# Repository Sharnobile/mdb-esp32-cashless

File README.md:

<div align="center">

# VMflow

### Open-Source Vending Machine IoT Platform

**Turn any vending machine into a connected, cashless, remotely managed device.**

**[🌐 Live Dashboard](https://app.kerl-handel.de)** · [⚡ Web Installer](https://app.kerl-handel.de/install) · [📖 Local Dev](DEV.md) · [🚀 Production](PROD.md) · [🏗 Architecture](ARCHITECTURE.md)

</div>

---

VMflow is a complete, **self-hostable** platform for retrofitting ordinary vending machines with modern IoT capabilities. A custom **ESP32-S3** board plugs into any machine's **MDB (Multi-Drop Bus)** and instantly unlocks cashless payments, real-time sales tracking, remote credit delivery, over-the-air firmware updates, warehouse-driven refills, foot-traffic analytics, and AI-powered insights — all controlled from a modern web dashboard and a native iOS app.

No vendor lock-in, no cloud subscription, no per-device fees. You own the hardware, the firmware, the backend, and the data.

---

## ✨ What You Can Do

<table>
<tr>
<td width="50%" valign="top">

### 🏪 Fleet & Machine Management
Monitor every machine in real time — online/offline status, today/this-week/this-month revenue, sales counts, and which machines need refilling. Drill into any machine for a 30-day revenue chart and an itemized, time-stamped sales history.

</td>
<td width="50%" valign="top">

### 💳 Cashless Payments (MDB)
A standards-compliant MDB **cashless peripheral**. Deliver credit to a machine remotely over MQTT or BLE, sit alongside existing coin/bill acceptors, and approve vends in real time. All payloads are XOR-encrypted with replay protection.

</td>
</tr>
<tr>
<td width="50%" valign="top">

### 📦 Warehouse & Inventory
Barcode-driven stock intake, **FIFO batch tracking** with expiry dates, per-warehouse minimum-stock alerts, stock-value reporting, and physical position layouts. Stock auto-decrements on every sale.

</td>
<td width="50%" valign="top">

### 🔁 Guided Refill Tours
A step-by-step refill wizard generates per-machine packing lists from live warehouse stock, walks the operator through the route, deducts inventory FIFO, and logs the whole tour for history and audit.

</td>
</tr>
<tr>
<td width="50%" valign="top">

### 🤖 AI Insights
Per-machine and fleet-wide recommendations powered by the **Claude API** — spot dead slots, surface best-sellers, and get concrete product-swap suggestions, in your own language. Bring your own API key.

</td>
<td width="50%" valign="top">

### 🧾 Sales Reconciliation
Upload a **Nayax** sales export and reconcile it against recorded sales with a time-tolerant matcher. Bulk-import anything missing, remove ghost entries, and export a CSV diff — fully audited.

</td>
</tr>
<tr>
<td width="50%" valign="top">

### 📊 Telemetry & Foot Traffic
Read **EVA-DTS DEX/DDCMP** data straight off the machine, count nearby foot traffic with the **PAX Counter** (anonymized BLE/WiFi presence), and keep a full MDB bus diagnostics + state history per device.

</td>
<td width="50%" valign="top">

### 🔄 OTA & Firmware
Build firmware in **GitHub Actions**, import a release with one click, and deploy **over-the-air** to any device over MQTT. Full/app-only images, version notes, and per-version rollout control.

</td>
</tr>
<tr>
<td width="50%" valign="top">

### 📡 Resilient Connectivity
WiFi out of the box, with optional **Cellular / LTE** (SIM7080G Cat-M / NB-IoT) for machines without a network. A multi-layer recovery ladder keeps devices online unattended in the field.

</td>
<td width="50%" valign="top">

### 🏢 Multi-Tenancy & Security
Organization-based access with **admin/viewer** roles, email invitations, and **row-level security** on every table. Self-hosted auth, storage, and database — your data never leaves your server.

</td>
</tr>
</table>

---

## 🖥 Management Dashboard

A modern, responsive web app (Nuxt 4 PWA, installable, dark mode, English & German) that gives operators full control over their fleet.

> **[👉 See it live at app.kerl-handel.de](https://app.kerl-handel.de)**

<table>
<tr>
<td width="50%" align="center" valign="top">

**Fleet overview** — live status, per-machine revenue, and stock urgency at a glance

</td>
<td width="50%" align="center" valign="top">

**Machine detail** — 30-day revenue chart and itemized sales history with product images

</td>
</tr>
<tr>
<td width="50%" align="center" valign="top">

**Product analysis** — springboard layout colour-coded by performance, with one-click swaps

</td>
<td width="50%" align="center" valign="top">

**Warehouse** — stock levels, FIFO batches, expiry warnings, and live stock value

</td>
</tr>
<tr>
<td width="50%" align="center" valign="top">

**Guided refill tour** — per-machine packing lists driven by live warehouse availability

</td>
<td width="50%" align="center" valign="top">

**Product catalog** — images, categories, pricing, and bulk Nayax import

</td>
</tr>
<tr>
<td width="50%" align="center" valign="top">

**Dashboard** — revenue KPIs, 7-day trend, and best-selling products

</td>
<td width="50%" align="center" valign="top">

**Firmware & OTA** — import from GitHub releases and deploy over-the-air

</td>
</tr>
</table>

---

## 📱 iOS App

A native **SwiftUI** app for operators — full fleet management from your pocket.

- **Dashboard** — revenue KPIs, 30-day sales chart, recent-sales feed
- **Machines** — sorted by stock urgency, with warehouse-availability labels
- **Trays & Stock** — per-machine slot configuration and quick stock adjustments
- **Refill Wizard** — warehouse-aware packing, guided refill tour, and a review step
- **Sales Stats** — today / yesterday / this week / last week per machine

Built with SwiftUI, Swift Concurrency, the Supabase Swift SDK, and Swift Charts. See [`ios/README.md`](ios/README.md) for setup.

<!--
  📸 iOS SCREENSHOTS
  Drop device screenshots into docs/screenshots/ios/ and uncomment the gallery below.

<table>
<tr>
<td width="33%" align="center"><br/><b>Dashboard</b></td>
<td width="33%" align="center"><br/><b>Machines</b></td>
<td width="33%" align="center"><br/><b>Refill Wizard</b></td>
</tr>
</table>
-->

> 📲 _App screenshots are being added — coming soon._

---

## 🤖 Android App

A native Android app is on the roadmap. **Coming soon.**

---

## 🔌 Hardware

The custom PCB connects directly to the vending machine's MDB bus via the standard connector. It's powered from the machine's own supply, needs no external power, and talks to the backend over WiFi (or optional Cellular/LTE) + MQTT.

<table>
<tr>
<td width="33%" align="center" valign="top">

**PCB v3** — latest revision

</td>
<td width="33%" align="center" valign="top">

**Installed** — with 3D-printed mount

</td>
<td width="33%" align="center" valign="top">

**Mounting bracket** — printable STL included

</td>
</tr>
</table>

**Key specs**

- **MCU:** ESP32-S3 (dual-core, WiFi + BLE 5)
- **MDB interface:** UART 9600 baud, 9-bit mode, optocoupler isolated
- **Power:** drawn from the vending-machine bus (onboard buck converter)
- **Connectivity:** WiFi, optional Cellular/LTE (SIM7080G Cat-M / NB-IoT)
- **Connectors:** MDB, USB-C (programming & debug), DEX telemetry port
- **PCB design:** KiCad — sources in [`kicad/`](kicad/)
- **Enclosure:** 3D-printable bracket — STL/STEP in [`3d-printing/`](3d-printing/)

> 🛒 **Order the PCB:** [PCBWay shared project](https://www.pcbway.com/project/shareproject/mdb_esp32_cashless_bc6bf8d8.html)

---

## 🏗 How It Works

```
┌───────────────────────────────────────────────────────────────────┐
│                       Management UI (Nuxt 4)  ·  iOS App (SwiftUI)  │
│            Dashboard · Machines · Warehouse · Refill · Firmware     │
└──────────────────────────────┬────────────────────────────────────┘
                               │ HTTPS
                               ▼
┌─────────────────────────────────────────────────────────────────────┐
│                       Supabase (self-hosted)                          │
│   ┌──────────┐  ┌──────────┐  ┌────────────────┐  ┌───────────────┐  │
│   │  Kong    │  │  Auth    │  │ Edge Functions  │  │   Storage     │  │
│   │ API GW   │  │ (GoTrue) │  │     (Deno)      │  │ firmware/imgs │  │
│   └──────────┘  └──────────┘  └────────┬────────┘  └───────────────┘  │
│   ┌─────────────────────────────────────────────────────────────┐    │
│   │            PostgreSQL  (RLS + multi-tenancy)                 │    │
│   └─────────────────────────────────────────────────────────────┘    │
└──────────────────────────────┬────────────────────────────────────────┘
                               │
            ┌──────────────────┼──────────────────┐
            ▼                  ▼                  ▼
┌──────────────────┐  ┌──────────────┐  ┌──────────────────────┐
│  MQTT Forwarder  │  │ MQTT Broker  │  │   GitHub Actions     │
│     (Deno)       │  │ (Mosquitto)  │  │   CI/CD → Releases   │
│  MQTT → Webhook  │  │    :1883     │  │   (firmware builds)  │
└──────────────────┘  └──────┬───────┘  └──────────────────────┘
                             │  MQTT over WiFi / Cellular
              ┌──────────────┴──────────────┐
              ▼                             ▼
   ┌──────────────────────┐     ┌──────────────────────┐
   │   ESP32-S3 (Slave)   │     │   ESP32-S3 (Slave)   │
   │   MDB Cashless       │ ··· │   MDB Cashless       │
   │  ┌────────────────┐  │     │  ┌────────────────┐  │
   │  │ Vending Machine│  │     │  │ Vending Machine│  │
   │  └────────────────┘  │     │  └────────────────┘  │
   └──────────────────────┘     └──────────────────────┘
```

Devices publish sales, status, telemetry, and diagnostics to per-tenant MQTT topics (`/{company}/{device}/{event}`). A Deno forwarder bridges MQTT to a Supabase Edge Function that decrypts, validates, and writes to PostgreSQL. Sensitive payloads (credit, sales, config) are **XOR-encrypted** with an 18-byte passkey and an ±8-second timestamp window to prevent replay. See [ARCHITECTURE.md](ARCHITECTURE.md) for the full picture.

---

## 🚀 Getting Started

### 1. Flash the firmware

The easiest way — no build tools required:

👉 **[app.kerl-handel.de/install](https://app.kerl-handel.de/install)** — flash directly from your browser via Web Serial

Or build from source with ESP-IDF v5.x:

```bash
cd mdb-slave-esp32s3
. $IDF_PATH/export.sh
idf.py build flash monitor
```

### 2. Deploy the platform

Pick the setup that fits your use case:

| | **Local Development** | **Production** |
|---|---|---|
| **Guide** | 📖 [**DEV.md**](DEV.md) | 🚀 [**PROD.md**](PROD.md) |
| **Purpose** | Develop & test locally | Deploy for real devices |
| **Backend** | Supabase CLI (`supabase start`) | Docker Compose (`docker compose up`) |
| **Frontend** | `npm run dev` (hot reload) | Built & served via Docker |
| **Setup** | `supabase start` + `npm run dev` | `bash setup.sh` (one command) |

### 3. Provision a device

Once the platform is running:

1. Power on the ESP32 board → it creates a WiFi hotspot
2. Connect to the hotspot and open the captive portal → enter WiFi credentials + server URL
3. In the dashboard, go to **Devices** → generate a provisioning code
4. Enter the code on the device's captive portal
5. The device reboots, connects to MQTT, and appears in your dashboard

---

## 🔗 REST API

VMflow exposes a full REST API via Supabase. Authenticate with a JWT bearer token.

<details>
<summary><strong>Get a bearer token</strong></summary>

```bash
curl -X POST 'https://your-server:8000/auth/v1/token?grant_type=password' \
  -H "apikey: YOUR_ANON_KEY" \
  -H "Content-Type: application/json" \
  -d '{ "email": "you@example.com", "password": "your_password" }'
```
</details>

<details>
<summary><strong>Send credit to a machine</strong></summary>

```bash
curl -X POST 'https://your-server:8000/functions/v1/send-credit' \
  -H "apikey: YOUR_ANON_KEY" \
  -H "Authorization: Bearer YOUR_ACCESS_TOKEN" \
  -H "Content-Type: application/json" \
  -d '{ "subdomain": 51, "amount": 1.50 }'
```
</details>

<details>
<summary><strong>View sales</strong></summary>

```bash
curl -X GET 'https://your-server:8000/rest/v1/sales' \
  -H "apikey: YOUR_ANON_KEY" \
  -H "Authorization: Bearer YOUR_ACCESS_TOKEN"
```
</details>

<details>
<summary><strong>View devices</strong></summary>

```bash
curl -X GET 'https://your-server:8000/rest/v1/embeddeds' \
  -H "apikey: YOUR_ANON_KEY" \
  -H "Authorization: Bearer YOUR_ACCESS_TOKEN"
```
</details>

---

## 🗺 PAX Counter — Foot-Traffic Heatmap

Each device scans for nearby BLE/WiFi devices and reports anonymized presence counts, visualized as heatmaps for location-performance analysis.

---

## 📂 Project Structure

```
mdb-esp32-cashless/
├── mdb-slave-esp32s3/       # ESP32 firmware — MDB cashless peripheral
├── mdb-master-esp32s3/      # ESP32 firmware — VMC simulator (for testing)
├── management-frontend/     # Nuxt 4 management dashboard (PWA)
├── ios/                     # Native iOS app (SwiftUI)
├── Docker/                  # Self-hosted backend (docker-compose)
│   ├── supabase/            # Edge functions, migrations, config
│   ├── mqtt/                # Mosquitto broker + Deno forwarder
│   └── setup.sh             # One-command production setup
├── kicad/                   # PCB design files (KiCad)
├── 3d-printing/             # Mounting bracket (STL/STEP/F3D)
├── docs/                    # Screenshots & documentation assets
├── .github/workflows/       # CI/CD — automated firmware builds
├── DEV.md                   # Local development guide
├── PROD.md                  # Production deployment guide
└── ARCHITECTURE.md          # System architecture details
```

---

## 🧰 Tech Stack

| Layer | Technology |
|-------|-----------|
| **Firmware** | ESP-IDF v5.x, FreeRTOS, NimBLE, MQTT, SIM7080G (cellular) |
| **Backend** | Supabase (PostgreSQL, GoTrue, PostgREST, Kong, Edge Functions) |
| **Edge Functions** | Deno (TypeScript) |
| **Frontend** | Nuxt 4, TypeScript, shadcn-vue, TailwindCSS 4, PWA, i18n (en/de) |
| **MQTT** | Eclipse Mosquitto + custom Deno forwarder |
| **AI** | Claude API (machine & fleet insights) |
| **PCB** | KiCad |
| **CI/CD** | GitHub Actions (ESP-IDF builds → GitHub Releases) |
| **iOS App** | SwiftUI, Swift Concurrency, Supabase Swift SDK, Swift Charts |

---

## 🤝 Contributing

Contributions are welcome — firmware, dashboard features, PCB revisions, docs, or bug fixes.

1. **Fork** the repository
2. Set up your [local development environment](DEV.md)
3. Create a feature branch (`git checkout -b feature/my-feature`)
4. Make your changes and ensure the build passes
5. Open a Pull Request

---

## 🙏 Acknowledgments

VMflow began as a fork of **[nodestark/mdb-esp32-cashless](https://github.com/nodestark/mdb-esp32-cashless)**.

Huge thanks to **[@nodestark](https://github.com/nodestark)** for the original open-source MDB cashless implementation for the ESP32 — the protocol foundation that everything here is built on. This project would not exist without that work. 🙌

---

## 📄 License

Licensed under the **MIT License** — see [LICENSE](LICENSE).

Original work Copyright © 2025 Nodestark. VMflow additions © 2025–2026 the VMflow contributors.

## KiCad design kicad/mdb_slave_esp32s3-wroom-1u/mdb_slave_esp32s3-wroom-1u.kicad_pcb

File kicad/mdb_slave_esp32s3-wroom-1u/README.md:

# MDB ESP32-S3 Cashless Module

Custom PCB adding cashless payment and telemetry to vending machines via the **MDB (Multi-Drop Bus)** protocol. Built around an **ESP32-S3-WROOM-1U** module with external antenna. Designed in KiCad 10.

Target platform: any vending machine equipped with an MDB bus. Backend (Supabase + MQTT + Nuxt, Dockerized) is out of scope for this repo.

Base reference: [lucienkerl/mdb-esp32-cashless](https://github.com/lucienkerl/mdb-esp32-cashless).

## Status

- Schematic: complete — ERC has 4 minor housekeeping items left (floating power symbols / an
  unconnected test pad, no real connectivity impact)
- PCB layout: routed, 4-layer board, 149.8 × 38.5 mm — schematic and PCB are in sync (all
  references renumbered and re-synced in rev1.4, including the previously-orphaned 1-Wire
  pull-up R4)
- Revision: **1.4.1** (R26/R28 changed from 10KΩ to 1KΩ)
- Gerbers in `gerber_to_order/` (JLCPCB, PCBWay) reflect the current board

## Overview

The board sits between the vending machine's MDB bus and a cashless payment terminal / telemetry stack. It reads and drives the machine's MDB peripherals, exposes auxiliary sensor and actuator interfaces (1-Wire, I2C, relays, custom digital inputs), and connects to WiFi for backend communication.

Key design decisions:

- **ESP32-S3-WROOM-1U-N16R2** module (16MB flash / 2MB PSRAM) with external u.FL antenna, chosen over a bare ESP32-S3 die because vending machine enclosures are often metal and block internal WiFi.
- **4-layer PCB**, for a dedicated ground/power plane structure and better EMI control around the switching regulator and MDB interface.
- All field connectors placed at the board edge for easy wiring and to fit inside a 3D-printed enclosure.
- Physical separation between the MDB (isolated, high-voltage) side and the logic side, matching the optocoupler isolation barrier in the schematic.

## Functional blocks

**MCU — U1**
ESP32-S3-WROOM-1U-N16R2, with EN/BOOT reset circuit (buttons B1/B2, pull-ups R1/R2/R10, decoupling C1–C3). Onboard WS2812B-compatible RGB status LED (LED1, driven by GPIO21).

**Power**
- F2: PTC resettable fuse on the incoming MDB-side supply
- U8: AP63201WU-7 buck converter, input 3.8V–32V, output 3.3V — **adjustable-output part** (rev1.4, replaces the fixed-output AP63203QWU-7), set by an external feedback divider: R23 (196kΩ, top) / R24 (62kΩ, bottom), with C19 (100pF) as feed-forward capacitor across R23
- C6 (10µF input), C7 (100nF bootstrap), C8/C9 (2×22µF output), L1 (3.3µH inductor)
- Switching loop (U8–L1–output) kept as compact as possible — primary EMI concern

**USB-C — USBC1**
USB 2.0 receptacle for programming/debug, with D6 Schottky diode against VBUS backfeed and R21/R22 CC pull-downs.

**MDB interface — H1**
2×3 connector. Galvanically isolated via U5/U6 (TLP785 optocouplers, DIP-4) on TX (GPIO4) and RX (GPIO5), with D2/D3 and associated pull-up/series resistors. F1 is the PTC resettable fuse on the incoming MDB-side supply.

**Relay outputs — P8, P9** *(added rev1.3)*
Two 15A-class SPDT relays (K2, K3 — SRD-03VDC-SL-C, 3V coil on the +3V3 rail), each output exposed as a 3-pin COM/NO/NC screw terminal. Each coil is driven low-side by an MMBT3904 transistor (Q2/Q3) with a 1N4148WS flyback diode (D4/D5), itself switched through a TLP785 optocoupler (U3/U4, SMD-4) for GPIO isolation:
- P8: Relay #1 — K2 / Q2 / U3, driven from GPIO1
- P9: Relay #2 — K3 / Q3 / U4, driven from GPIO2

⚠️ Known open point: with the current TLP785 pull-up/pull-down arrangement, drive logic is inverted (GPIO low, or floating at boot, = relay energized; GPIO high = relay de-energized). Confirm this matches firmware expectations, or flip the pull-up/pull-down before ordering if a fail-safe de-energized default is required.

**1-Wire buses — P4, P5, P6**
Two 1-Wire interfaces plus a spare/parallel header, each with a pull-up resistor:
- P6: bus #1 (GPIO15)
- P5: bus #2 (GPIO16)
- P4: spare header on bus #1 (GPIO15)

**Custom digital inputs — P1, P2, P3**
Three screw-terminal inputs with pull-up resistors: P1 (GPIO6), P2 (GPIO17), P3 (GPIO18).

**I2C — J3**
JST XH 1×4 connector with pull-ups, SCL on GPIO11, SDA on GPIO10.

**Debug / programming**
- J1: UART debug header (1×6) — EN, TXD, RXD, IO0, GND, +3V3
- J2: JTAG header (1×6) — MTMS, MTDI, MTDO, MTCk, GND, +3V3

**Other**
- TH1: NTC thermistor input (GPIO7)
- BUZZER1: buzzer, driven by GPIO12 through Q1
- H2–H5: mounting holes
- H6–H10: test/probe pads (H8 taps the WS2812B LED1 data-out, H10 the buzzer driver)
- GPIO3: reserved for firmware-based PCB/board detection

## Connectors summary

| Ref | Function | Type |
|---|---|---|
| USBC1 | USB-C (program/debug) | USB2.0 16P receptacle |
| J1 | UART debug | 1×6 pin header |
| J2 | JTAG | 1×6 pin header |
| J3 | I2C | 1×4 JST XH |
| P1, P2, P3 | Custom digital inputs (×3) | 3-pin screw terminal, 5.08mm |
| P4, P5, P6 | 1-Wire buses (bus #1 spare, bus #2, bus #1) | 3-pin screw terminal, 5.08mm |
| P8 | Relay #1 output (COM/NO/NC) | 3-pin screw terminal, 5.08mm |
| P9 | Relay #2 output (COM/NO/NC) | 3-pin screw terminal, 5.08mm |
| H1 | MDB bus | 2×3 connector, isolated |

## Repository structure

```
mdb_slave_esp32s3-wroom-1u/
├── mdb_slave_esp32s3-wroom-1u.kicad_pro   KiCad project
├── mdb_slave_esp32s3-wroom-1u.kicad_sch   Schematic
├── mdb_slave_esp32s3-wroom-1u.kicad_pcb   PCB layout (routed, rev 1.4.1)
├── gerber_to_order/                       Fabrication Gerbers per vendor (JLCPCB, PCBWay) — versioned
└── production/                            BOM, CPL, netlist (generated locally, not versioned)
```

The `.kicad_pro` / `.kicad_sch` / `.kicad_pcb` files, this README, and `gerber_to_order/` are
version-controlled — see `.gitignore`.

## Tools

- KiCad 10.0.4
- JLCPCB / PCBWay for fabrication, assembly, and component sourcing

## License

*(add license — e.g. CERN-OHL-S, MIT for firmware, etc.)*

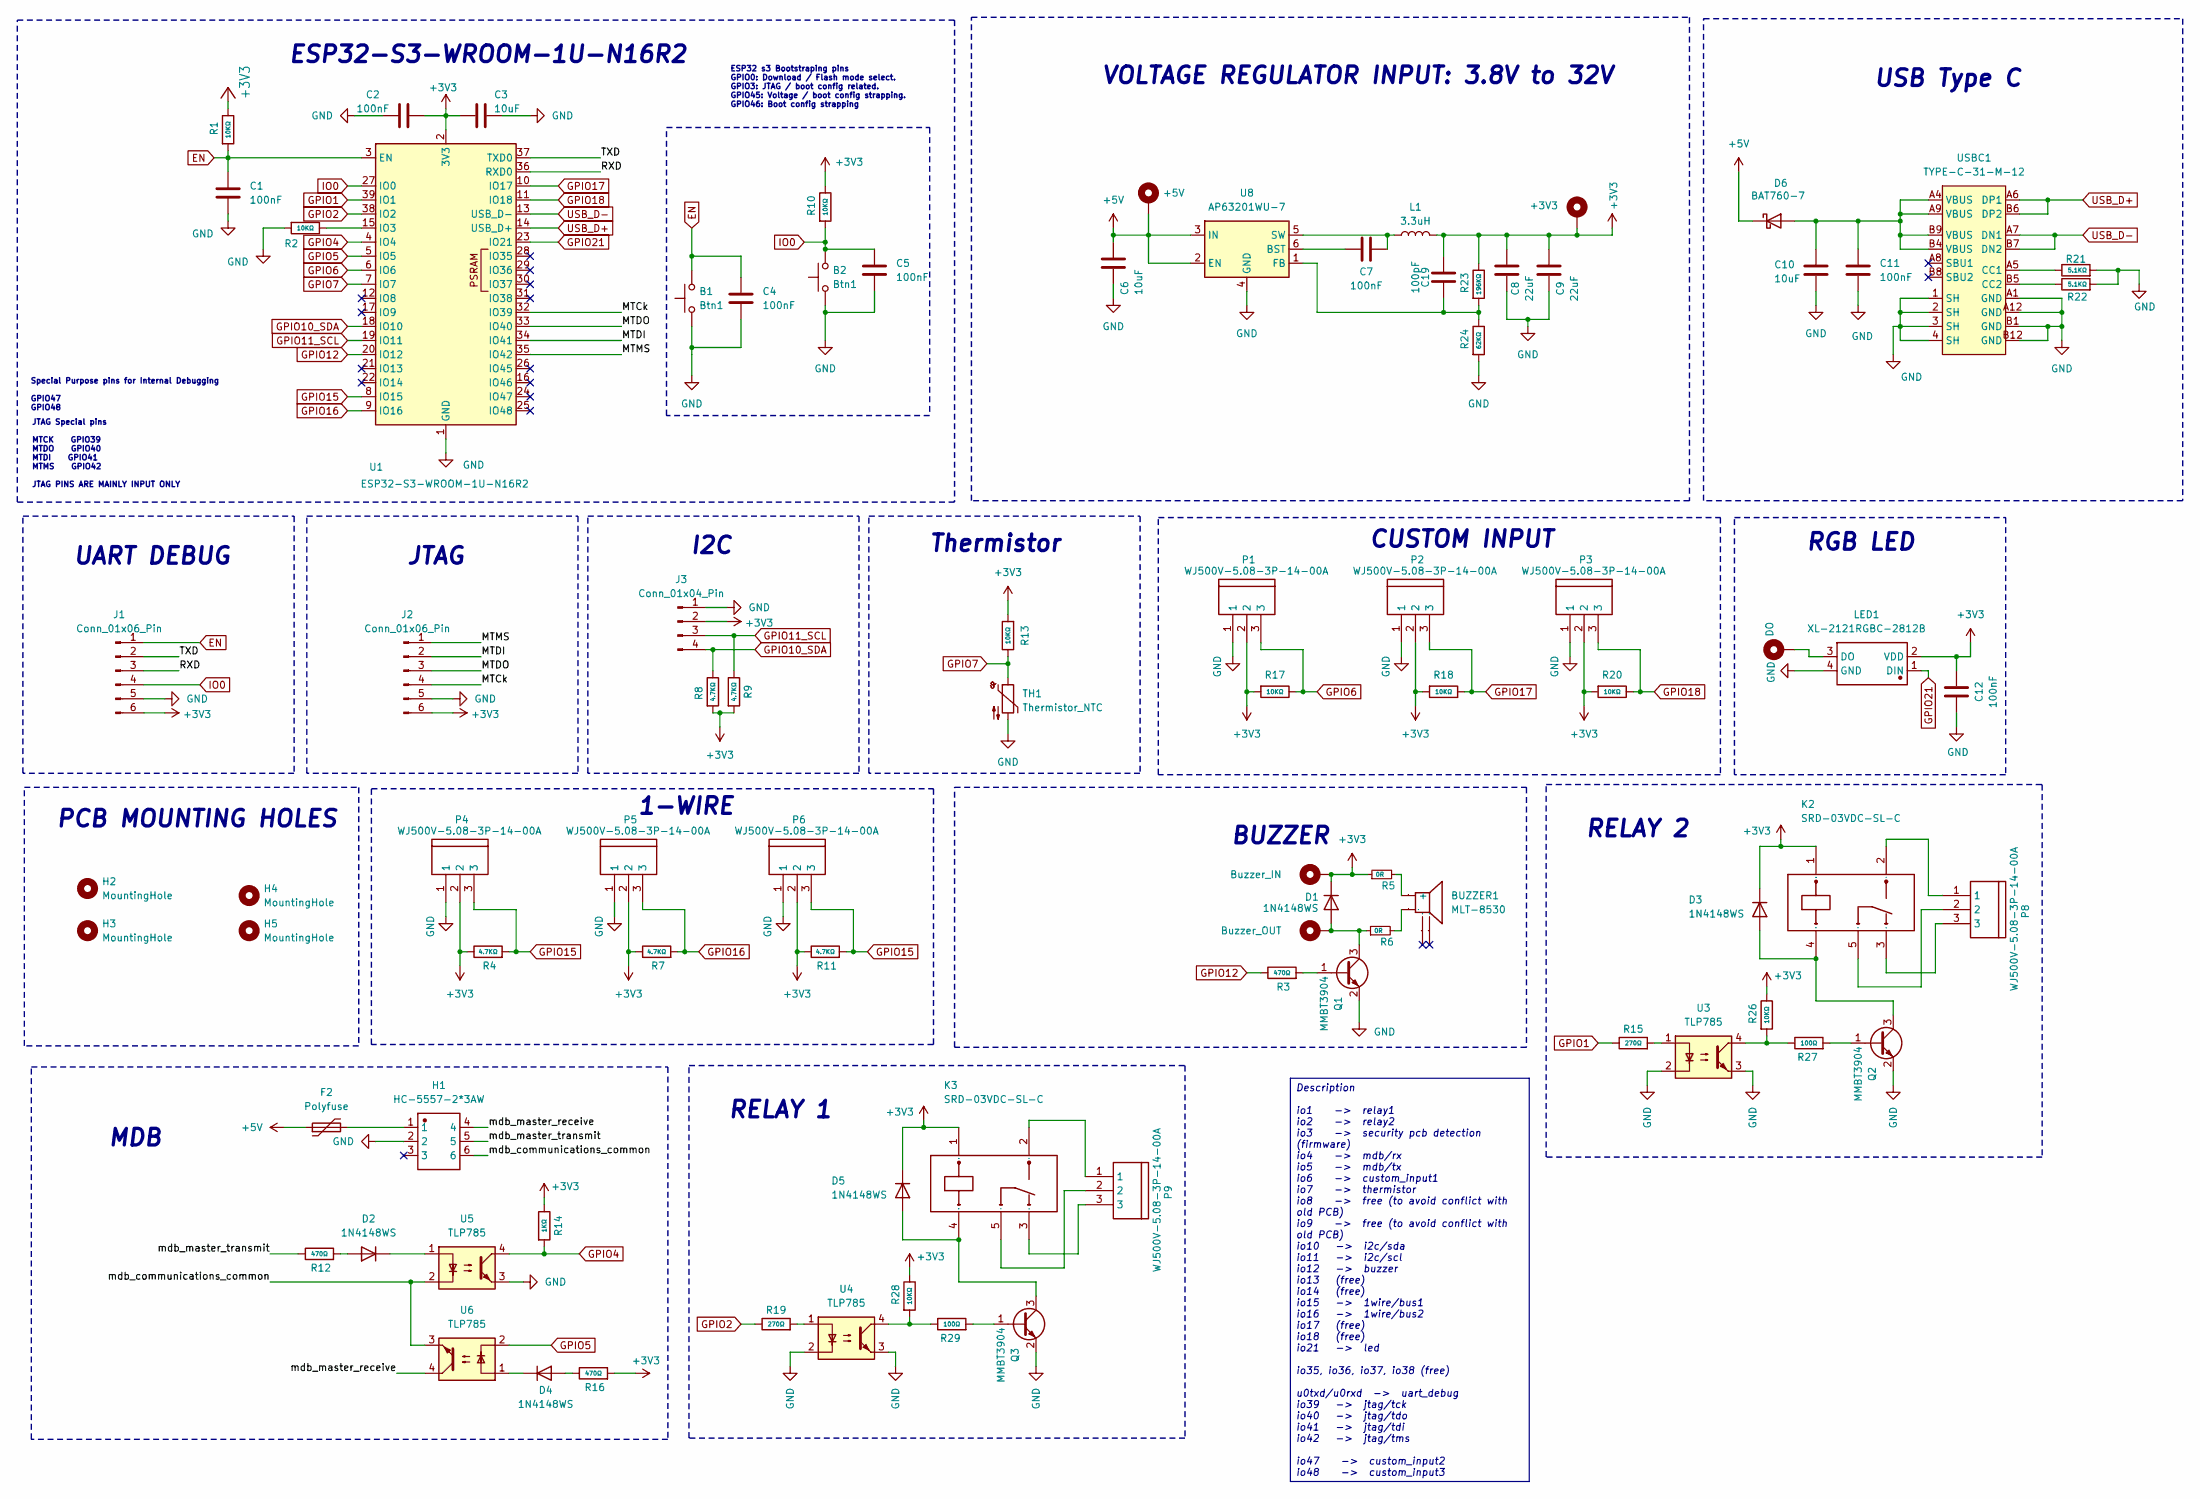
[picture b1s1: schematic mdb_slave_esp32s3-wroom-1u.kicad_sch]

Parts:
B1, B2: Btn1; KEY-SMD_B3U-1000PM; MFR.Part # B3U-1000P; LCSC C231329
BUZZER1: MLT-8530; BUZ-SMD_4P-L8.5-W8.5-P8.50-BR_C94599; MFR.Part # MLT-8530; LCSC C94599
C1, C2, C4, C5, C7, C11, C12: 100nF; C_0603_1608Metric; MFR.Part # CC0603KRX7R9BB104; LCSC C14663
C3, C6, C10: 10uF; C_0603_1608Metric; MFR.Part # CL10A106KP8NNNC; LCSC C19702
C8, C9: 22uF; C_0603_1608Metric; MFR.Part # CL10A226MQ8NRNC; LCSC C59461
C19: 100pF; C_0603_1608Metric; MFR.Part # CL10C101JB8NNNC; LCSC C14858
D1, D2, D3, D4, D5: 1N4148WS; D_SOD-323; MFR.Part # 1N4148WS; LCSC C2128
D6: BAT760-7; D_SOD-323; MFR.Part # BAT760-7; LCSC C27636120
F2: Polyfuse; C_1812_4532Metric; MFR.Part # 1812L110/33GR; LCSC C7542972
H1: HC-5557-2*3AW; CONN-TH_6P-P4.20-S5.50_5557-2X3AW_C2845788; MFR.Part # HC-5557-2*3AW; LCSC C2845788
H2, H3, H4, H5: MountingHole; MountingHole_2.7mm_M2.5_ISO7380
H6: +5V; TestPoint_Pad_D1.0mm
H7: +3V3; TestPoint_Pad_D1.0mm
H8: DO; TestPoint_Pad_D1.0mm
H9: Buzzer_IN; TestPoint_Pad_D1.0mm
H10: Buzzer_OUT; TestPoint_Pad_D1.0mm
J1, J2: Conn_01x06_Pin; PinSocket_1x06_P2.54mm_Vertical; LCSC C37208
J3: Conn_01x04_Pin; JST_XH_B4B-XH-A_1x04_P2.50mm_Vertical; MFR.Part # B4B-XH-A(LF)(SN); LCSC C144395
K2, K3: SRD-03VDC-SL-C; RELAY-TH_SRD-XXVDC-XL-C_C24585; MFR.Part # SRD-03VDC-SL-C; LCSC C24585
L1: 3.3uH; L_0603_1608Metric; MFR.Part # SDFL1608S6R8KTF; LCSC C75929
LED1: XL-2121RGBC-2812B; LED-SMD_4P-L2.1-W2.1-BR_XL-2121RGBC-WS2812B_C5349957; MFR.Part # XL-2121RGBC-2812B; LCSC C5349957
P1, P2, P3, P4, P5, P6, P8, P9: WJ500V-5.08-3P-14-00A; CONN-TH_3P-P5.00_WJ500V-5.08-3P_C72334; MFR.Part # WJ500V-5.08-03P-14-00A; LCSC C72334
Q1, Q2, Q3: MMBT3904; SOT-23; MFR.Part # MMBT3904; LCSC C916374
R1, R2, R10, R13, R17, R18, R20, R26, R28: 10KΩ; R_0603_1608Metric; MFR.Part # 0603WAF1002T5E; LCSC C25804
R3, R12, R16: 470Ω; R_0603_1608Metric; MFR.Part # 0603WAF4700T5E; LCSC C23179
R4, R7, R8, R9, R11: 4.7KΩ; R_0603_1608Metric; MFR.Part # 0603WAF4701T5E; LCSC C23162
R5, R6: 0R; R_0603_1608Metric_Pad0.98x0.95mm_HandSolder; MFR.Part # 0603WAF0000T5E; LCSC C21189
R14: 1KΩ; R_0603_1608Metric; MFR.Part # RC0603JR-071KL; LCSC C14676
R15, R19: 270Ω; R_0603_1608Metric; MFR.Part # 0603WAF2700T5E; LCSC C22966
R21, R22: 5.1KΩ; R_0603_1608Metric; MFR.Part # 0603WAF5101T5E; LCSC C23186
R23: 196KΩ; R_0603_1608Metric; MFR.Part # 0603WAF1963T5E; LCSC C22930
R24: 62KΩ; R_0603_1608Metric; MFR.Part # 0603WAF6202T5E; LCSC C23221
R27, R29: 100Ω; R_0603_1608Metric; MFR.Part # 0603WAF1000T5E; LCSC C22775
TH1: Thermistor_NTC; C_0603_1608Metric_Pad1.08x0.95mm_HandSolder; MFR.Part # NCP18XH103F03RB; LCSC C13564
U1: ESP32-S3-WROOM-1U-N16R2; WIRELM-SMD_ESP32-S3-WROOM-1U_C3013945; MFR.Part # ESP32-S3-WROOM-1U-N16R2; LCSC C3013945
U3, U4, U5, U6: TLP785; SMD-4_L4.6-W6.5-P2.54-LS10.2-BR_C45445; MFR.Part # TLP785(GB-TP6,F; LCSC C45445
U8: AP63201WU-7; TSOT-23-6; MFR.Part # AP63201WU-7; LCSC C2071044
USBC1: TYPE-C-31-M-12; USB-C_SMD-TYPE-C-31-M-12; MFR.Part # TYPE-C-31-M-12; LCSC C165948

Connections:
+3V3: C2.2, C3.2, C8.2, C9.2, C12.2, C19.1, D1.1 (K), D3.1 (K), D5.1 (K), H7.1, H9.1, J1.6, J2.6, J3.2, K2.1, K3.1, L1.2, LED1.2 (VDD), P1.2, P2.2, P3.2, P4.2, P5.2, P6.2, R1.1, R4.1, R5.1, R7.1, R8.2, R9.2, R10.1, R11.1, R13.2, R14.1, R16.2, R17.2, R18.2, R20.2, R23.1, R26.1, R28.1, U1.2 (3V3)
+5V: C6.1, D6.1 (K), F2.1, H6.1, U8.2 (EN), U8.3 (IN)
/MTCk: J2.4, U1.32 (IO39)
/MTDI: J2.2, U1.34 (IO41)
/MTDO: J2.3, U1.33 (IO40)
/MTMS: J2.1, U1.35 (IO42)
/RXD: J1.3, U1.36 (RXD0)
/TXD: J1.2, U1.37 (TXD0)
/mdb_communications_common: H1.6, U5.2, U6.3
/mdb_master_receive: H1.4, U6.4
/mdb_master_transmit: H1.5, R12.1
EN: B1.2, C1.1, C4.1, J1.1, R1.2, U1.3 (EN)
GND: B1.1, B2.1, C1.2, C2.1, C3.1, C4.2, C5.2, C6.2, C8.1, C9.1, C10.2, C11.2, C12.1, H1.2, J1.5, J2.5, J3.1, LED1.4 (GND), P1.1, P2.1, P3.1, P4.1, P5.1, P6.1, Q1.2 (E), Q2.2 (E), Q3.2 (E), R2.2, R21.2, R22.2, R24.2, TH1.2, U1.1 (GND), U1.40 (GND), U1.41 (GND), U3.2, U3.3, U4.2, U4.3, U5.3, U8.4 (GND), USBC1.1 (SH), USBC1.2 (SH), USBC1.3 (SH), USBC1.4 (SH), USBC1.A1 (GND), USBC1.A12 (GND), USBC1.B1 (GND), USBC1.B12 (GND)
GPIO1: R15.1, U1.39 (IO1)
GPIO2: R19.1, U1.38 (IO2)
GPIO4: R14.2, U1.4 (IO4), U5.4
GPIO5: U1.5 (IO5), U6.2
GPIO6: P1.3, R17.1, U1.6 (IO6)
GPIO7: R13.1, TH1.1, U1.7 (IO7)
GPIO10_SDA: J3.4, R8.1, U1.18 (IO10)
GPIO11_SCL: J3.3, R9.1, U1.19 (IO11)
GPIO12: R3.1, U1.20 (IO12)
GPIO15: P4.3, P6.3, R4.2, R11.2, U1.8 (IO15)
GPIO16: P5.3, R7.2, U1.9 (IO16)
GPIO17: P2.3, R18.1, U1.10 (IO17)
GPIO18: P3.3, R20.1, U1.11 (IO18)
GPIO21: LED1.1 (DIN), U1.23 (IO21)
IO0: B2.2, C5.1, J1.4, R10.2, U1.27 (IO0)
unnamed: BUZZER1.1 (+), R5.2
unnamed: BUZZER1.2, R6.2
unnamed: D1.2 (A), H10.1, Q1.3 (C), R6.1
unnamed: D2.2 (A), R12.2
unnamed: D2.1 (K), U5.1
unnamed: D3.2 (A), K2.4, Q2.3 (C)
unnamed: D4.2 (A), R16.1
unnamed: D4.1 (K), U6.1
unnamed: D5.2 (A), K3.4, Q3.3 (C)
unnamed: C10.1, C11.1, D6.2 (A), USBC1.A4 (VBUS), USBC1.A9 (VBUS), USBC1.B4 (VBUS), USBC1.B9 (VBUS)
unnamed: F2.2, H1.1
unnamed: K2.2, P8.1
unnamed: K2.3, P8.3
unnamed: K2.5, P8.2
unnamed: K3.2, P9.1
unnamed: K3.3, P9.3
unnamed: K3.5, P9.2
unnamed: H8.1, LED1.3 (DO)
unnamed: Q1.1 (B), R3.2
unnamed: Q2.1 (B), R27.2
unnamed: Q3.1 (B), R29.2
unnamed: R15.2, U3.1
unnamed: R19.2, U4.1
unnamed: R26.2, R27.1, U3.4
unnamed: R28.2, R29.1, U4.4
unnamed: R2.1, U1.15 (IO3)
unnamed: C7.1, U8.6 (BST)
unnamed: C19.2, R23.2, R24.1, U8.1 (FB)
unnamed: C7.2, L1.1, U8.5 (SW)
unnamed: R21.1, USBC1.A5 (CC1)
unnamed: R22.1, USBC1.B5 (CC2)
USB_D+: U1.14 (USB_D+), USBC1.A6 (DP1), USBC1.B6 (DP2)
USB_D-: U1.13 (USB_D-), USBC1.A7 (DN1), USBC1.B7 (DN2)

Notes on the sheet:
MDB
Special Purpose pins for Internal Debugging GPIO47 GPIO48
RGB LED
RELAY 1
PCB MOUNTING HOLES
1-WIRE
Thermistor
CUSTOM INPUT
UART DEBUG
I2C
USB Type C
BUZZER
ESP32-S3-WROOM-1U-N16R2
RELAY 2
JTAG
JTAG Special pins MTCK GPIO39 MTDO GPIO40 MTDI GPIO41 MTMS GPIO42 JTAG PINS ARE MAINLY INPUT ONLY
ESP32 s3 Bootstraping pins GPIO0: Download / Flash mode select. GPIO3: JTAG / boot config related. GPIO45: Voltage / boot config strapping. GPIO46: Boot config strapping
VOLTAGE REGULATOR INPUT: 3.8V to 32V
Description io1 -> relay1 io2 -> relay2 io3 -> security pcb detection (firmware) io4 -> mdb/rx io5 -> mdb/tx io6 -> custom_input1 io7 -> thermistor io8 -> free (to avoid conflict with old PCB) io9 -> free (to avoid conflict with old PCB) io10 -> i2c/sda io11 -> i2c/scl io12 -> buzzer io13 (free) io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

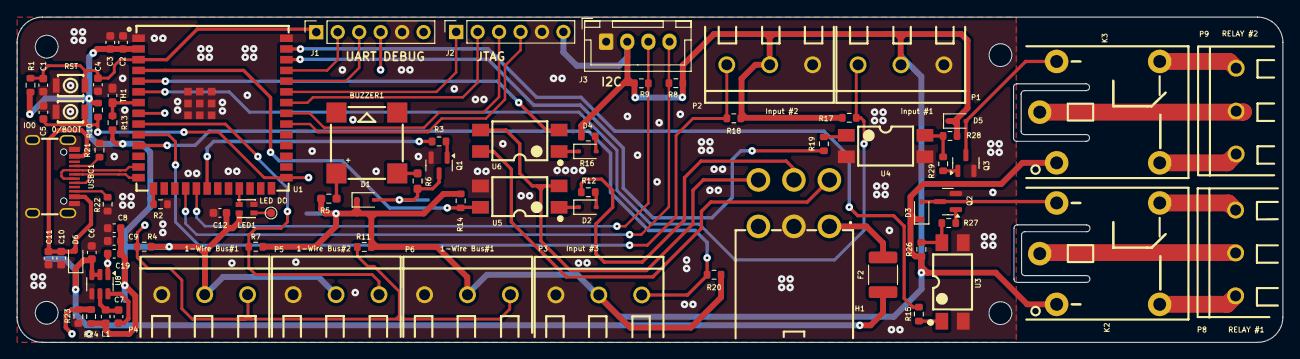
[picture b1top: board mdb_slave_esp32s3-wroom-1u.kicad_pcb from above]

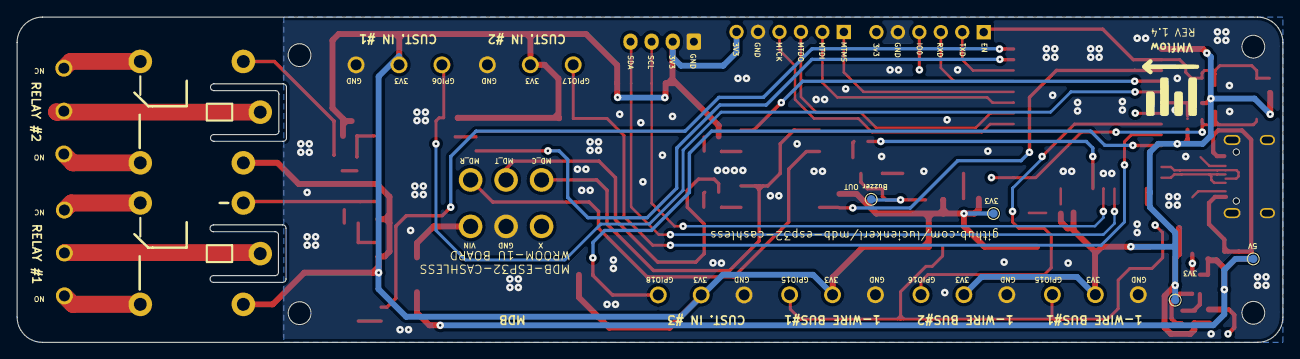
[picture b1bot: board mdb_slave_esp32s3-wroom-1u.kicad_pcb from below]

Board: 4 copper layers, 149.8 x 38.5 mm, 87 parts (4 on the bottom side), 61 nets.

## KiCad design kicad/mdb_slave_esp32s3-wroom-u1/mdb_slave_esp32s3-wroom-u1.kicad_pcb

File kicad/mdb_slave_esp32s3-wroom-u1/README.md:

# MDB ESP32-S3 Cashless Module

Custom PCB adding cashless payment and telemetry to vending machines via the **MDB (Multi-Drop Bus)** protocol. Built around an **ESP32-S3-WROOM-1U** module with external antenna. Designed in KiCad 10.

Target platform: any vending machine equipped with an MDB bus. Backend (Supabase + MQTT + Nuxt, Dockerized) is out of scope for this repo.

Base reference: [lucienkerl/mdb-esp32-cashless](https://github.com/lucienkerl/mdb-esp32-cashless).

## Status

- Schematic: **complete, ERC-clean** (0 errors, 0 warnings)
- PCB layout: **not started** — components placed on one side of the board only, no routing yet
- Revision: 1.0

## Overview

The board sits between the vending machine's MDB bus and a cashless payment terminal / telemetry stack. It reads and drives the machine's MDB peripherals, exposes auxiliary sensor and actuator interfaces (1-Wire, I2C, relays, pulse, generic I/O), and connects to WiFi for backend communication.

Key design decisions:

- **ESP32-S3-WROOM-1U-N16R2** module (16MB flash / 2MB PSRAM) with external u.FL antenna, chosen over a bare ESP32-S3 die because vending machine enclosures are often metal and block internal WiFi.
- **4-layer PCB**, for a dedicated ground/power plane structure and better EMI control around the switching regulator and MDB interface.
- All field connectors placed at the board edge for easy wiring and to fit inside a 3D-printed enclosure.
- Physical separation between the MDB (isolated, high-voltage) side and the logic side, matching the optocoupler isolation barrier in the schematic.

## Functional blocks

**MCU — U1**
ESP32-S3-WROOM-1U-N16R2, with reset/boot circuit (SW1, pull-ups R1/R2, decoupling C1). Onboard WS2812B RGB status LED (D2).

**Power**
- F1: PTC resettable fuse (1.1A / 33V) on the incoming MDB-side supply
- U2: AP63203QWU-7 buck converter, output 3.3V
- C3 (10µF input), C4 (bootstrap), C5/C6 (2×22µF output), L1 (3.3µH inductor)
- Switching loop (U2–L1–output) kept as compact as possible — primary EMI concern

**USB-C — J1**
USB 2.0 receptacle for programming/debug, with D1 Schottky diode against VBUS backfeed and R3/R4 CC pull-downs.

**MDB interface — J12**
2×3 Molex-style connector. Galvanically isolated via U3/U4 (TLP785 optocouplers) on TX and RX, with D5/D6 and associated pull-up/series resistors.

**Relay outputs — J2, J3**
Two independent outputs, each driven by an MMBT3904 transistor (Q1/Q2) with a Schottky flyback diode (D3/D4) and base resistor.

**Pulse output — J8**
MMBT3904 (Q3) driver stage for a single pulse-type output.

**1-Wire buses — J4, J5, J6**
Two (plus a spare header) 1-Wire interfaces with pull-up resistors, for temperature or other 1-Wire sensors.

**I2C — J10**
JST PH 1×4 connector with pull-ups, for external I2C peripherals.

**Generic digital inputs — J11, J13, J14**
Three screw-terminal inputs with pull-up resistors.

**Debug / programming**
- J9: UART header (4-pin)
- J7: JTAG header (6-pin)

**Other**
- TH1: NTC thermistor input
- BUZZER1: buzzer with series resistor
- H1–H5: mounting holes

## Connectors summary

| Ref | Function | Type |
|---|---|---|
| J1 | USB-C (program/debug) | USB2.0 16P receptacle |
| J2, J3 | Relay outputs (×2) | 2-pin screw terminal |
| J4, J5, J6 | 1-Wire buses | 3-pin screw terminal |
| J7 | JTAG | 1×6 pin header |
| J8 | Pulse output | 1×3 pin header (JST) |
| J9 | UART debug | 1×4 pin header |
| J10 | I2C | 1×4 JST PH |
| J11, J13, J14 | Generic digital input (×3) | 3-pin screw terminal |
| J12 | MDB bus | 2×3 connector, isolated |

## Repository structure

```
/schematic      KiCad schematic (.kicad_sch)
/pcb            KiCad PCB layout (.kicad_pcb) — in progress
/gerbers        Fabrication output (once layout is finalized)
/bom            Bill of materials (LCSC references)
```

*(adjust to match actual repo layout)*

## Tools

- KiCad 10.0.4
- JLCPCB / PCBWay for fabrication, assembly, and component sourcing

## License

*(add license — e.g. CERN-OHL-S, MIT for firmware, etc.)*

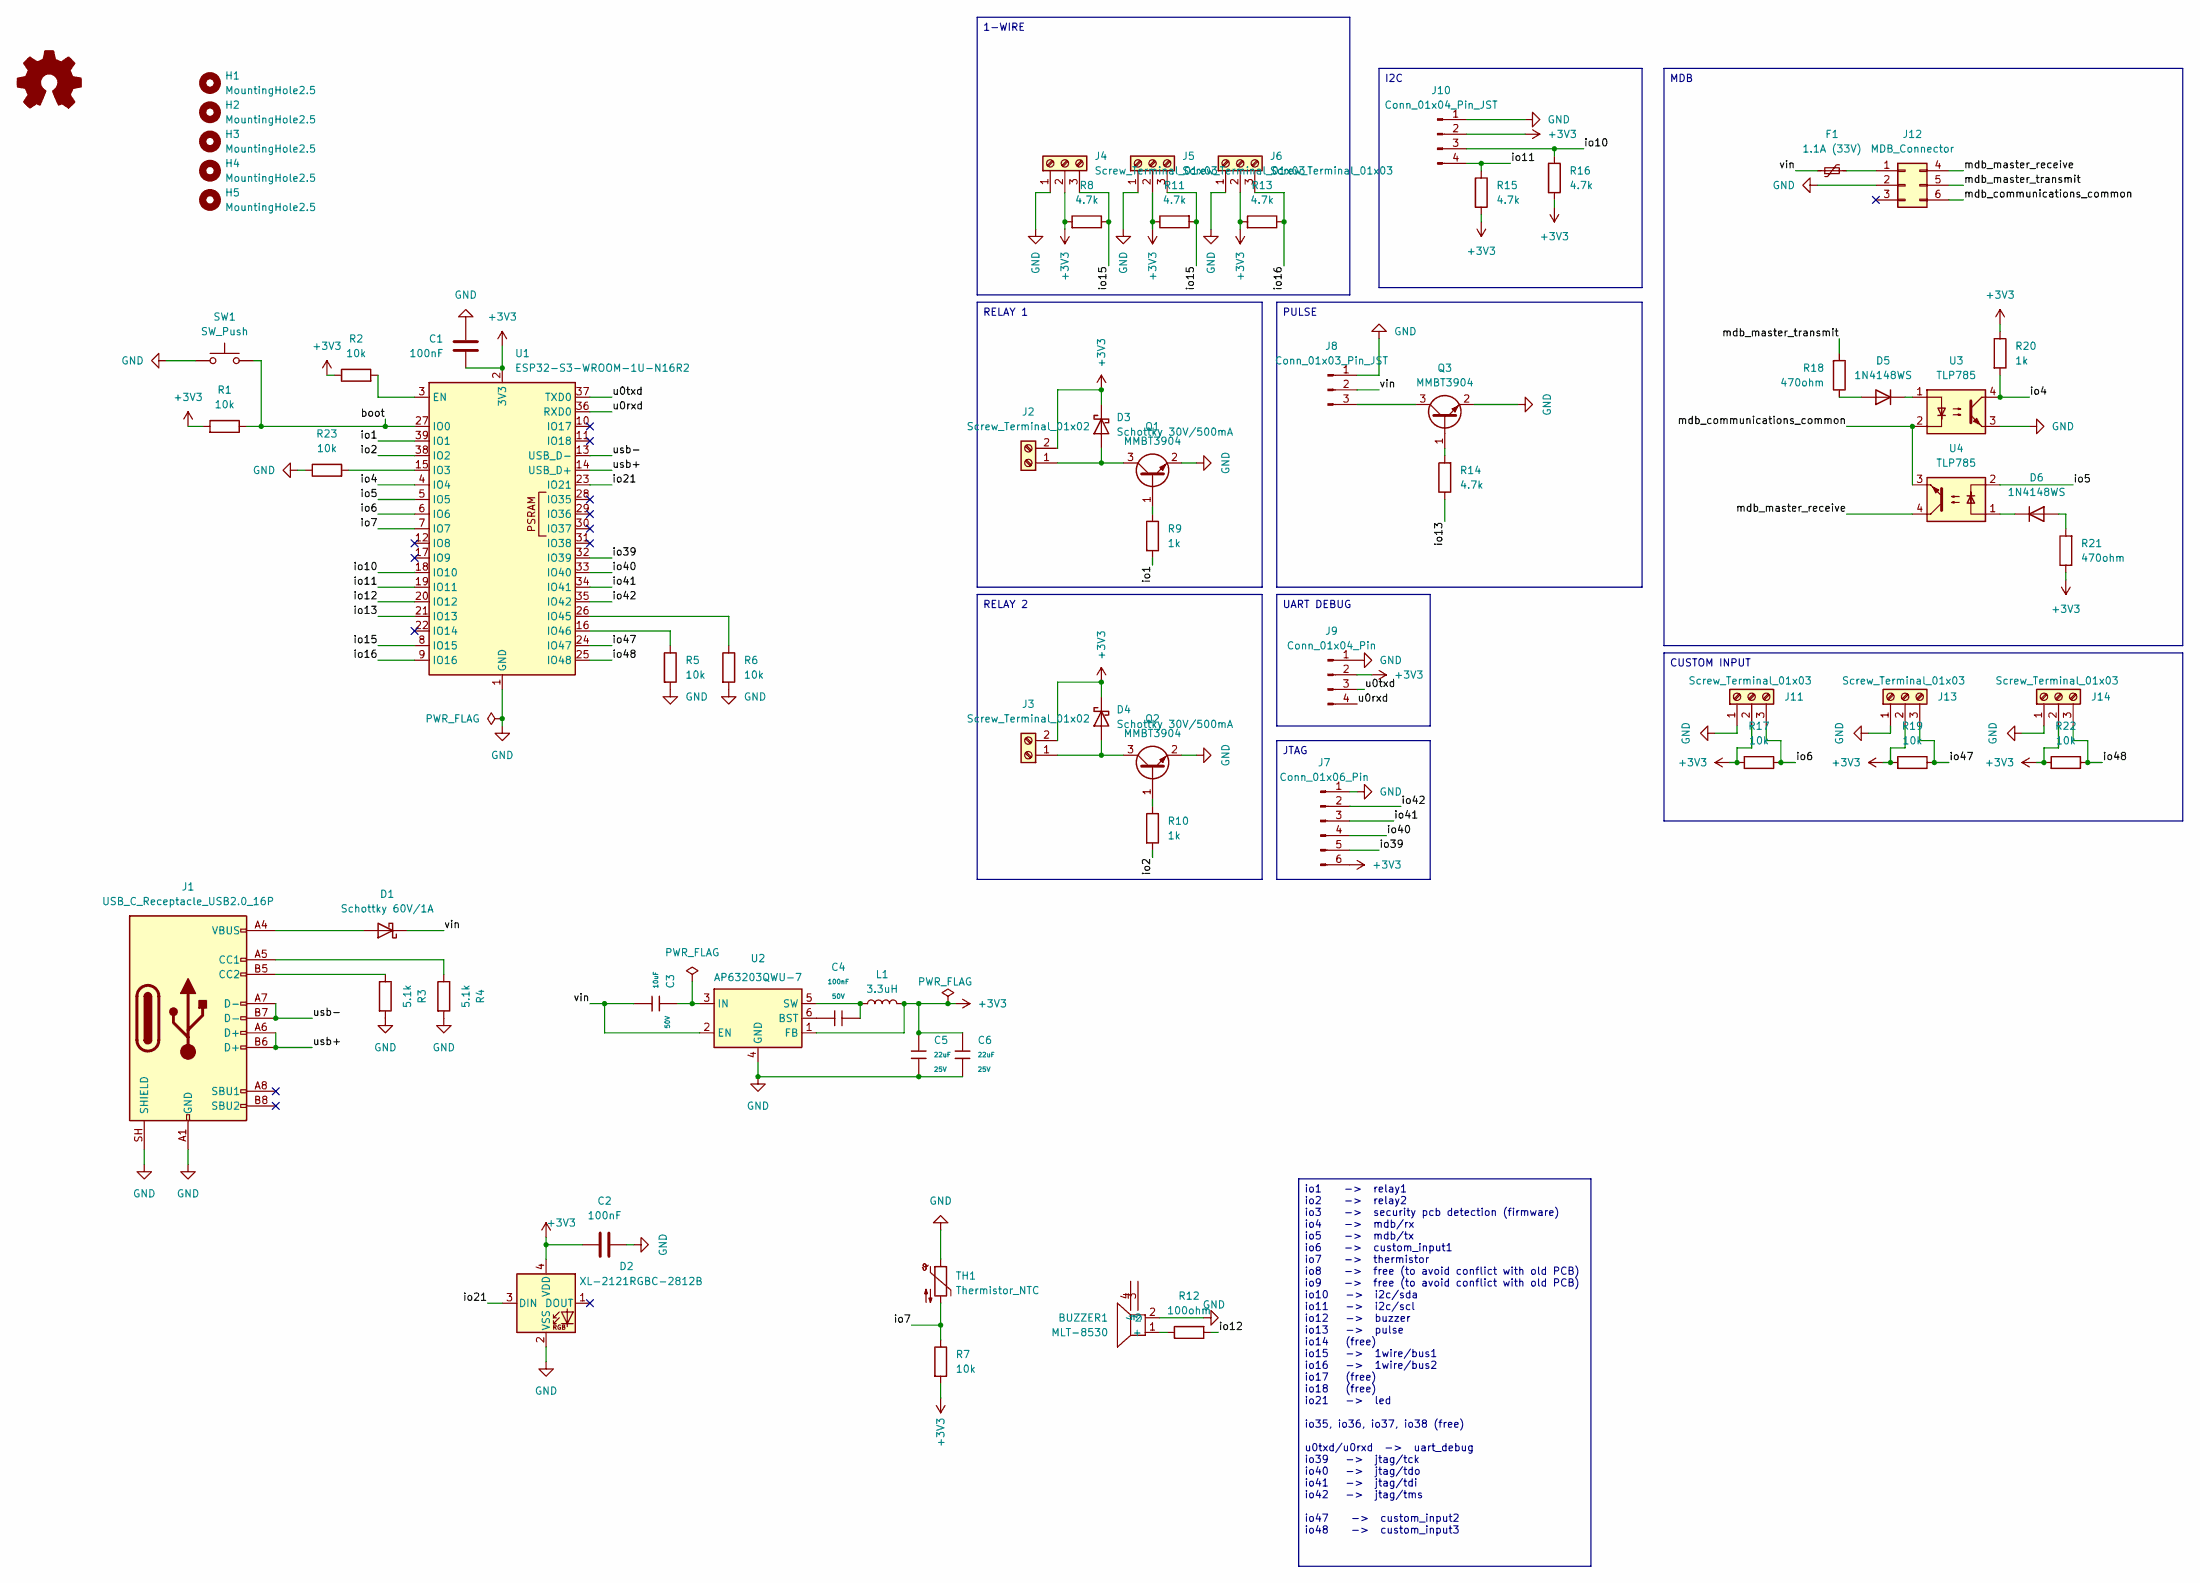
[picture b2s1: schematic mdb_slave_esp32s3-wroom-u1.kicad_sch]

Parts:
BUZZER1: MLT-8530; BUZ-SMD_4P-L8.5-W8.5-P8.50-BR; MPN MLT-8530; LCSC# C94599
C1, C2: 100nF; C_0603_1608Metric; LCSC# C14663
C3: 10uF; C_0603_1608Metric; Voltage Rated 50V; Tolerance ±10%; Part 0603B103K500NT; LCSC# C19702
C4: 100nF; C_0603_1608Metric; Voltage Rated 50V; Tolerance ±10%; Part CC0603KRX7R9BB104; LCSC# C14663
C5, C6: 22uF; C_0603_1608Metric; Voltage Rated 25V; Tolerance ±10%; Part CL10B224KA8NNNC; LCSC# C59461
D1: Schottky 60V/1A; D_SOD-123; LCSC# C64894
D2: XL-2121RGBC-2812B; LED_WS2812B-2020_PLCC4_2.0x2.0mm; LCSC# C5349957
D3, D4: Schottky 30V/500mA; D_SOD-123; LCSC# C437999
D5, D6: 1N4148WS; D_SOD-323; LCSC# C2128
F1: 1.1A (33V); Fuse_1812_4532Metric; LCSC# C7542972
H1, H2, H3, H4, H5: MountingHole2.5
J1: USB_C_Receptacle_USB2.0_16P; USB_C_Receptacle_G-Switch_GT-USB-7010ASV; LCSC# C2988369
J2, J3: Screw_Terminal_01x02; CONN-TH_2P-P2.54_DIBO_DB141R-2.54-2P; LCSC# C2898754
J4, J5, J6, J11, J13, J14: Screw_Terminal_01x03; CONN-TH_3P-P2.54_DIBO_DB141R-2.54-3P; LCSC# C2898755
J7: Conn_01x06_Pin; PinHeader_1x06_P2.54mm_Vertical; LCSC# C37208
J8: Conn_01x03_Pin_JST; JST_PH_B3B-PH-K_1x03_P2.00mm_Vertical; LCSC# C131339
J9: Conn_01x04_Pin; PinHeader_1x04_P2.54mm_Vertical; LCSC# C124378
J10: Conn_01x04_Pin_JST; JST_PH_B4B-PH-K_1x04_P2.00mm_Vertical; LCSC# C131334
J12: MDB_Connector; Molex_Mini-Fit_Jr_5566-06A_2x03_P4.20mm_Vertical; LCSC# C2845778
L1: 3.3uH; L_TechFuse_SL0420; LCSC# C22463807
Q1, Q2, Q3: MMBT3904; SOT-23; LCSC# C916374
R1, R2, R5, R6, R7, R17, R19, R22, R23: 10k; R_0603_1608Metric; LCSC# C98220
R3, R4: 5.1k; R_0603_1608Metric; LCSC# C2907044
R8, R11, R13, R14, R15, R16: 4.7k; R_0603_1608Metric; LCSC# C23162
R9, R10, R20: 1k; R_0603_1608Metric; LCSC# C2907002
R12: 100ohm; R_0603_1608Metric; LCSC# C2906981
R18, R21: 470ohm; R_0603_1608Metric; LCSC# C22356627
SW1: SW_Push; SW_Tactile_SPST_NO_Straight_CK_PTS636Sx25SMTRLFS; LCSC# C42435421
TH1: Thermistor_NTC; R_0603_1608Metric; LCSC# C13564
U1: ESP32-S3-WROOM-1U-N16R2; WIRELM-SMD_ESP32-S3-WROOM-1U; LCSC# C3013945
U2: AP63203QWU-7; TSOT-23-6; LCSC# C5248536
U3, U4: TLP785; SMD-4_L4.6-W3.7-P2.54-LS7.0-BR; LCSC# C128776

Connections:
+3V3: C1.2, C2.2, C5.1, C6.1, D2.4 (VDD), D3.1 (K), D4.1 (K), J2.2, J3.2, J4.2, J5.2, J6.2, J7.6, J9.2, J10.2, J11.2, J13.2, J14.2, L1.2, R1.2, R2.1, R7.2, R8.2, R11.1, R13.2, R15.2, R16.2, R17.2, R19.2, R20.1, R21.1, R22.2, U1.2 (3V3), U2.1 (FB)
/boot: R1.1, SW1.1, U1.27 (IO0)
/io1: R9.2, U1.39 (IO1)
/io2: R10.2, U1.38 (IO2)
/io4: R20.2, U1.4 (IO4), U3.4
/io5: U1.5 (IO5), U4.2
/io6: J11.3, R17.1, U1.6 (IO6)
/io7: R7.1, TH1.2, U1.7 (IO7)
/io10: J10.3, R16.1, U1.18 (IO10)
/io11: J10.4, R15.1, U1.19 (IO11)
/io12: R12.2, U1.20 (IO12)
/io13: R14.1, U1.21 (IO13)
/io15: J4.3, J5.3, R8.1, R11.2, U1.8 (IO15)
/io16: J6.3, R13.1, U1.9 (IO16)
/io21: D2.3 (DIN), U1.23 (IO21)
/io39: J7.5, U1.32 (IO39)
/io40: J7.4, U1.33 (IO40)
/io41: J7.3, U1.34 (IO41)
/io42: J7.2, U1.35 (IO42)
/io47: J13.3, R19.1, U1.24 (IO47)
/io48: J14.3, R22.1, U1.25 (IO48)
/mdb_communications_common: J12.6, U3.2, U4.3
/mdb_master_receive: J12.4, U4.4
/mdb_master_transmit: J12.5, R18.2
/u0rxd: J9.4, U1.36 (RXD0)
/u0txd: J9.3, U1.37 (TXD0)
/usb+: J1.A6 (D+), J1.B6 (D+), U1.14 (USB_D+)
/usb-: J1.A7 (D-), J1.B7 (D-), U1.13 (USB_D-)
/vin: C3.1, D1.1 (K), F1.1, J8.2, U2.2 (EN)
GND: BUZZER1.2, C1.1, C2.1, C5.2, C6.2, D2.2 (VSS), J1.A1 (GND), J1.A12 (GND), J1.B1 (GND), J1.B12 (GND), J1.SH (SHIELD), J4.1, J5.1, J6.1, J7.1, J8.1, J9.1, J10.1, J11.1, J12.2, J13.1, J14.1, Q1.2 (E), Q2.2 (E), Q3.2 (E), R3.2, R4.2, R5.2, R6.2, R23.1, SW1.2, TH1.1, U1.1 (GND), U1.40 (GND), U1.41 (GND), U2.4 (GND), U3.3
unnamed: BUZZER1.1 (+), R12.1
unnamed: D1.2 (A), J1.A4 (VBUS), J1.A9 (VBUS), J1.B4 (VBUS), J1.B9 (VBUS)
unnamed: D3.2 (A), J2.1, Q1.3 (C)
unnamed: D4.2 (A), J3.1, Q2.3 (C)
unnamed: D5.2 (A), R18.1
unnamed: D5.1 (K), U3.1
unnamed: D6.2 (A), R21.2
unnamed: D6.1 (K), U4.1
unnamed: J1.A5 (CC1), R4.1
unnamed: J1.B5 (CC2), R3.1
unnamed: J8.3, Q3.3 (C)
unnamed: F1.2, J12.1
unnamed: Q1.1 (B), R9.1
unnamed: Q2.1 (B), R10.1
unnamed: Q3.1 (B), R14.2
unnamed: R2.2, U1.3 (EN)
unnamed: R23.2, U1.15 (IO3)
unnamed: R6.1, U1.26 (IO45)
unnamed: R5.1, U1.16 (IO46)
unnamed: C4.1, U2.6 (BST)
unnamed: C3.2, U2.3 (IN)
unnamed: C4.2, L1.1, U2.5 (SW)

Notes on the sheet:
UART DEBUG
io1 -> relay1 io2 -> relay2 io3 -> security pcb detection (firmware) io4 -> mdb/rx io5 -> mdb/tx io6 -> custom_input1 io7 -> thermistor io8 -> free (to avoid conflict with old PCB) io9 -> free (to avoid conflict with old PCB) io10 -> i2c/sda io11 -> i2c/scl io12 -> buzzer io13 -> pulse io14 (free) 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
PULSE
RELAY 2
JTAG
I2C
1-WIRE
CUSTOM INPUT
MDB
RELAY 1

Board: 2 copper layers, 66 parts (0 on the bottom side), 52 nets, no tracks yet.

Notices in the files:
README.md:
License: MIT
